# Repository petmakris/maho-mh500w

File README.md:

# Maho MH500w CNC

Documentation and notes for a Maho MH500W CNC

## Selecting Heidenhain EXE (converters for 

LS-403C has a grating period of 20μm ==> 1 μm resolution in 5 fold interpolation

# Linux CNC Installation

# Software Installation

Start of `bookworm/sid` (use xfce):

https://cdimage.debian.org/cdimage/unofficial/non-free/cd-including-firmware/

- Remove cdrom from sources: sudo nano /etc/sources.list
- `sudo apt install ethtool`

Check driver alignment:

- `lspci`
- `sudo ethtool -i enp2s0`

## Install Rods' custom kernel

6.1 exists in my NAS

- install headers
- install kernel
- `sudo apt install grub-customizer`
- `sudo apt install r8168-dkms`

# Mesa 7i97

## Network interface:

`sudo vim /etc/network/interfaces`

```
auto enp2s0
iface enp2s0 inet static
address 10.10.10.1 or 192.168.1.1
```
Restart network: `sudo systemctl restart networking`

`mesaflash --device 7i97 --addr 10.10.10.10 --readhmid`

# ??? sudo ethtool -C eth0 rx-usecs 0

# LinuxCNC

`sudo apt install linuxcnc-uspace linuxcnc-uspace-dev mesaflash`

Let it run for a while. While it is running,
in another window, check the network latency by reviewing the TMAX settings on your card

`halcmd show param hm2*tmax*`

```
Parameters:
Owner   Type  Dir         Value  Name
     7  s32   RW              0  hm2_7i97.0.read-request.tmax
     7  bit   RO          FALSE  hm2_7i97.0.read-request.tmax-increased
     7  s32   RW         704022  hm2_7i97.0.read.tmax
     7  bit   RO          FALSE  hm2_7i97.0.read.tmax-increased
     7  s32   RW          42126  hm2_7i97.0.write.tmax
     7  bit   RO          FALSE  hm2_7i97.0.write.tmax-increased
```

# Notes

[Enable outputs](https://forum.linuxcnc.org/27-driver-boards/46253-mesa-7i97-analog-out-issue#246257)

# Notes

- MAHO Original color: RAL6011

## Pull Stud

- SK40 ISO 7388 II B
  - The short pull stud for SK
  - The long for BT 

ISO Standard: https://www.iso.org/standard/68845.html

What fits to a CAT40 cone:
    Pull studs ISO 7388-3 Form UD | M16 | former norm ISO 7388 Form II B (https://bit.ly/38K9Pz4)
    Kemmler
        Order number: 404.20.16
        https://www.kemmler-shop.de/en/pull-studs/pull-studs-iso-7388/1509/pull-studs-iso-7388-3-form-ud-m16-with-drill-through-without-o-ring?c=1099

What fits to a BT40 cone:
    Longer by 3mm.
    Kemmler:
        Order number: 404.20.16.20
        https://www.kemmler-shop.de/en/pull-studs/pull-studs-iso-7388/1511/pull-studs-iso-7388-3-form-ud-m16-with-drill-through-incl.-o-ring?c=1099

# Gallery

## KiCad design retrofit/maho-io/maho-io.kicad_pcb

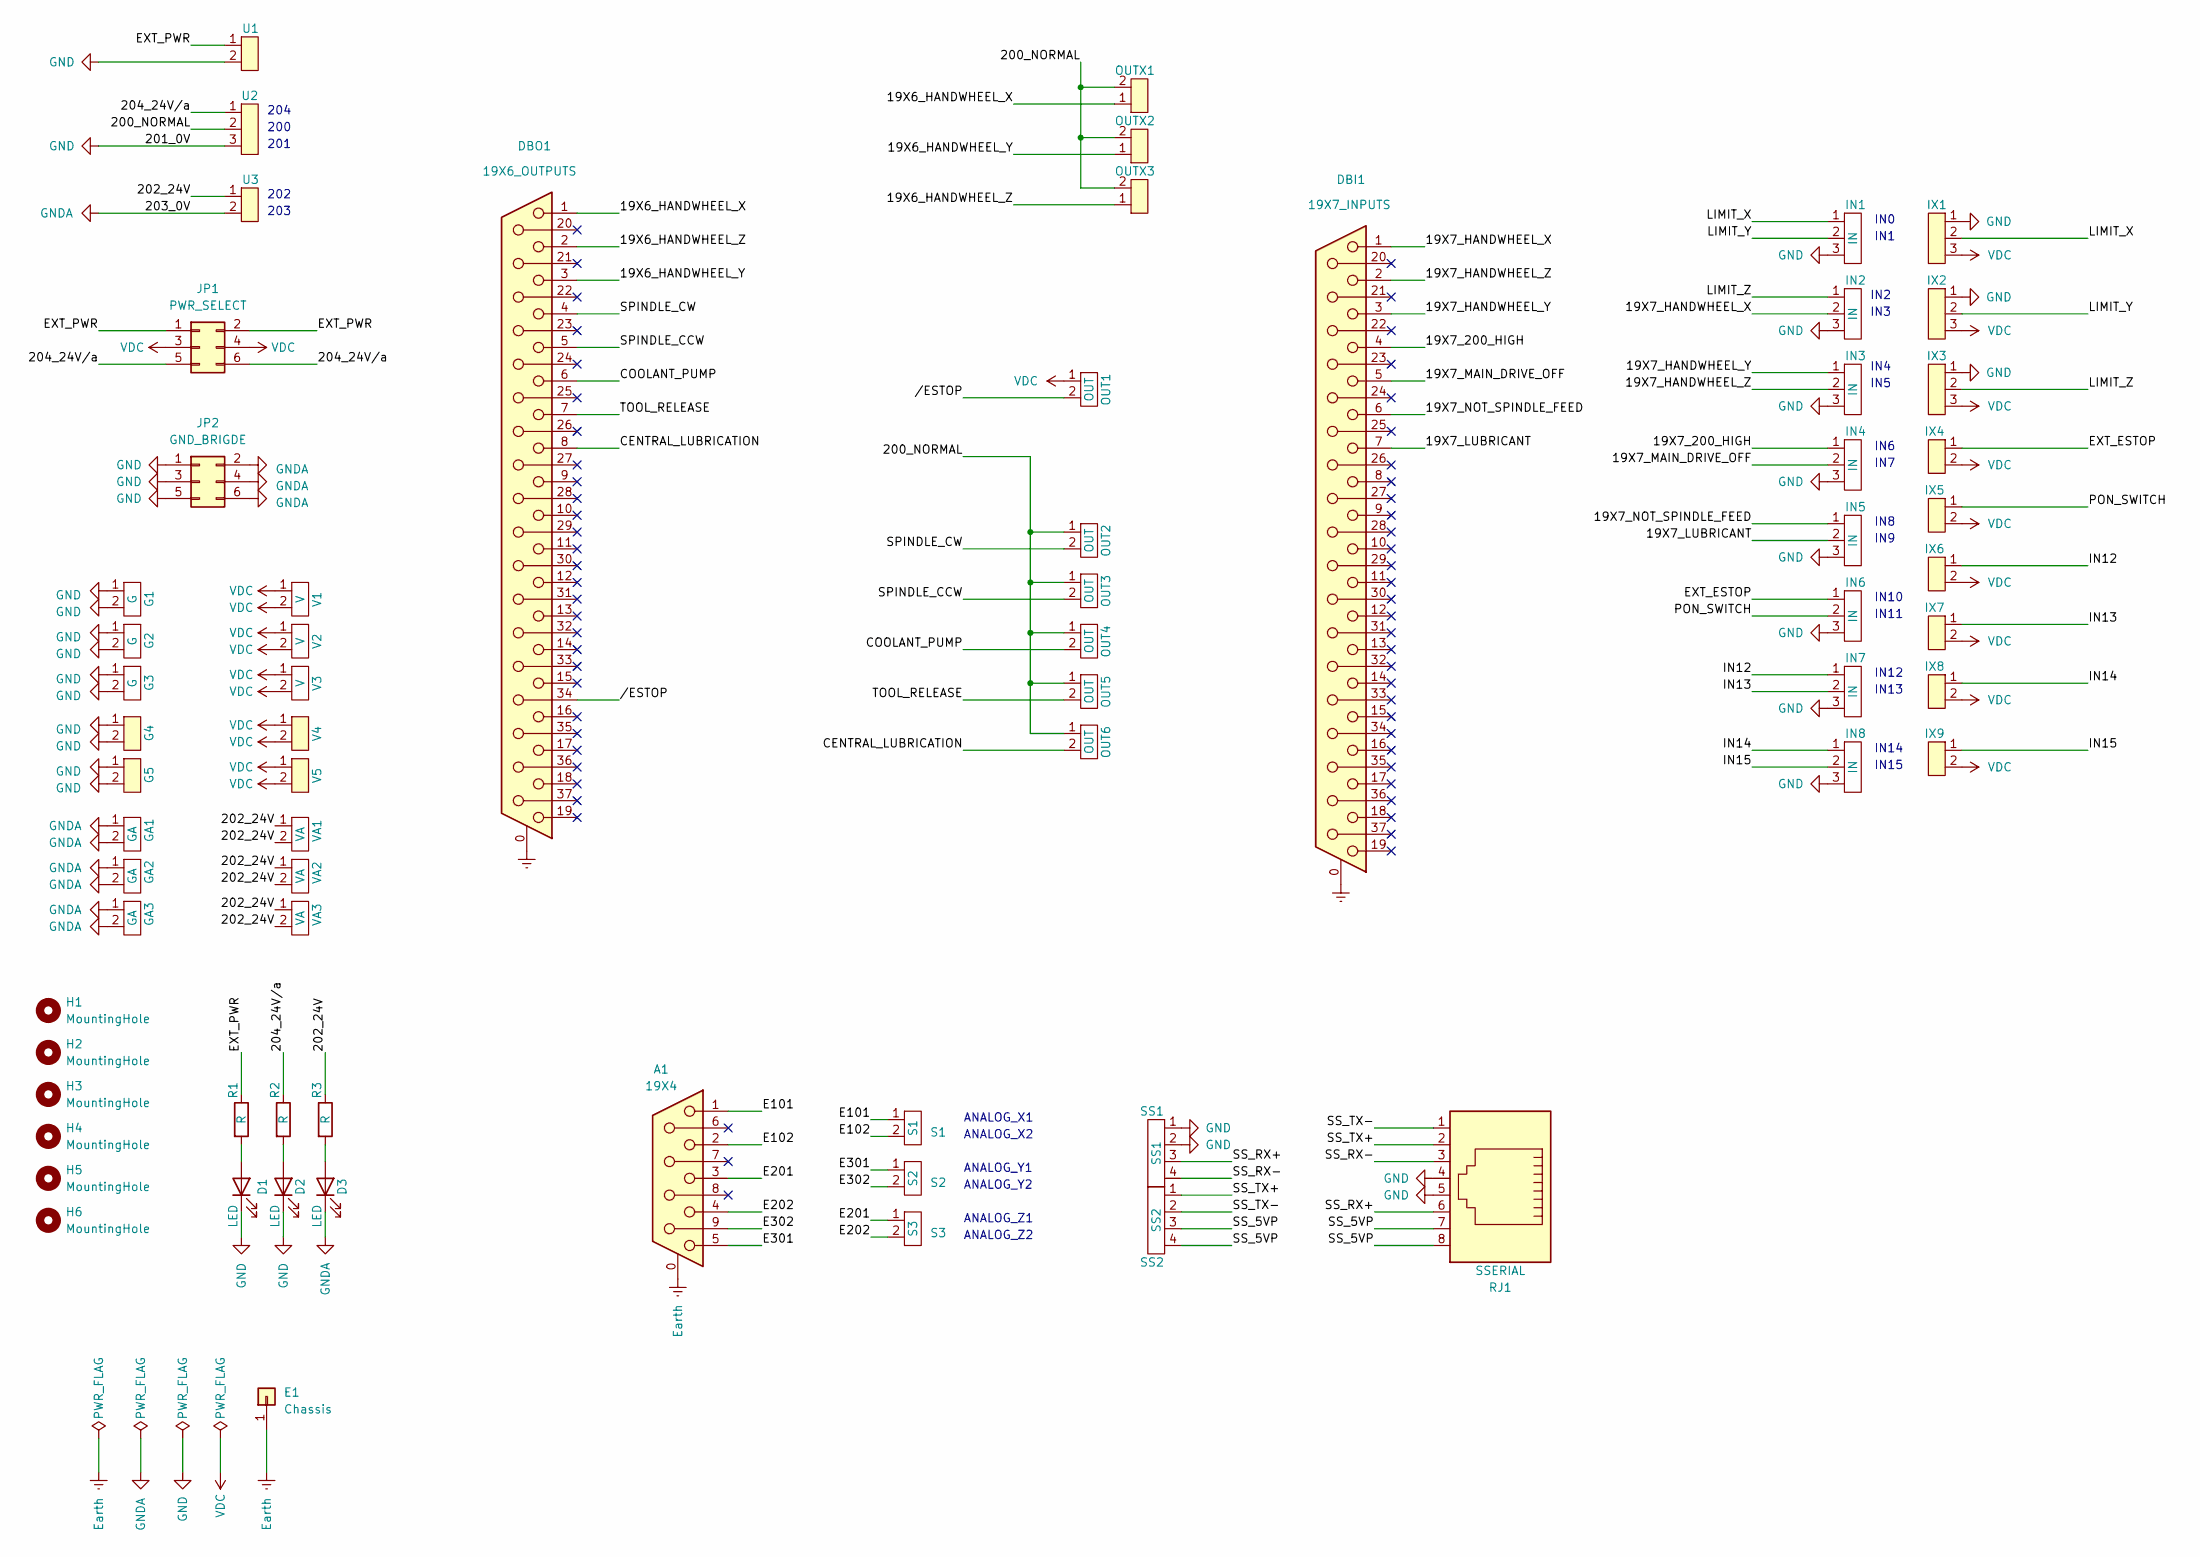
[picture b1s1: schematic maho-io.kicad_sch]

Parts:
A1: 19X4; DSUB-9_Female_Vertical_P2.77x2.84mm_MountingHoles
D1, D2, D3: LED; LED_D5.0mm
DBI1: 19X7_INPUTS; DSUB-37_Female_Vertical_P2.77x2.84mm_MountingHoles
DBO1: 19X6_OUTPUTS; DSUB-37_Female_Vertical_P2.77x2.84mm_MountingHoles
E1: Chassis; MountingHole_4.5mm_Pad
G1, G2, G3: G; XY2500V-C(5.08)-2P
G4, G5: XY2500R-C(5.08)-2P
GA1, GA2, GA3: GA; XY2500V-C(5.08)-2P
H1, H2, H3, H4, H5, H6: MountingHole; MountingHole_4.5mm
IN1, IN2, IN3, IN4, IN5, IN6, IN7, IN8: IN; XY2500V-C(5.08)-3P
IX1, IX2, IX3: XY2500R-C(5.08)-3P
IX4, IX5, IX6, IX7, IX8, IX9: XY2500R-C(5.08)-2P
JP1: PWR_SELECT; PinSocket_2x03_P2.54mm_Vertical
JP2: GND_BRIGDE; PinSocket_2x03_P2.54mm_Vertical
OUT1, OUT2, OUT3, OUT4, OUT5, OUT6: OUT; XY2500V-C(5.08)-2P
OUTX1, OUTX2, OUTX3: XY2500R-C(5.08)-2P
R1, R2, R3: R; R_0805_2012Metric
RJ1: SSERIAL; MTJ-88FX1
S1: S1; XY2500V-C(5.08)-2P
S2: S2; XY2500V-C(5.08)-2P
S3: S3; XY2500V-C(5.08)-2P
SS1: SS1; XY2500V-C(5.08)-4P
SS2: SS2; XY2500V-C(5.08)-4P
U1, U3: XY2500R-C(5.08)-2P
U2: XY2500R-C(5.08)-3P
V1, V2, V3: V; XY2500V-C(5.08)-2P
V4, V5: XY2500R-C(5.08)-2P
VA1, VA2, VA3: VA; XY2500V-C(5.08)-2P

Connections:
/19X6_HANDWHEEL_X: DBO1.1, OUTX1.1
/19X6_HANDWHEEL_Y: DBO1.3, OUTX2.1
/19X6_HANDWHEEL_Z: DBO1.2, OUTX3.1
/19X7_200_HIGH: DBI1.4, IN4.1
/19X7_HANDWHEEL_X: DBI1.1, IN2.2
/19X7_HANDWHEEL_Y: DBI1.3, IN3.1
/19X7_HANDWHEEL_Z: DBI1.2, IN3.2
/19X7_LUBRICANT: DBI1.7, IN5.2
/19X7_MAIN_DRIVE_OFF: DBI1.5, IN4.2
/19X7_NOT_SPINDLE_FEED: DBI1.6, IN5.1
/200_NORMAL: OUT2.1, OUT3.1, OUT4.1, OUT5.1, OUT6.1, OUTX1.2, OUTX2.2, OUTX3.2, U2.2
/202_24V: R3.1, U3.1, VA1.1, VA1.2, VA2.1, VA2.2, VA3.1, VA3.2
/204_24V/a: JP1.5, JP1.6, R2.1, U2.1
/CENTRAL_LUBRICATION: DBO1.8, OUT6.2
/COOLANT_PUMP: DBO1.6, OUT4.2
/E101: A1.1, S1.1
/E102: A1.2, S1.2
/E201: A1.3, S3.1
/E202: A1.4, S3.2
/E301: A1.5, S2.1
/E302: A1.9, S2.2
/EXT_ESTOP: IN6.1, IX4.1
/EXT_PWR: JP1.1, JP1.2, R1.1, U1.1
/IN12: IN7.1, IX6.1
/IN13: IN7.2, IX7.1
/IN14: IN8.1, IX8.1
/IN15: IN8.2, IX9.1
/LIMIT_X: IN1.1, IX1.2
/LIMIT_Ζ: IN2.1, IX3.2
/LIMIT_Υ: IN1.2, IX2.2
/PON_SWITCH: IN6.2, IX5.1
/SPINDLE_CCW: DBO1.5, OUT3.2
/SPINDLE_CW: DBO1.4, OUT2.2
/SS_5VP: RJ1.7, RJ1.8, SS2.3, SS2.4
/SS_RX+: RJ1.6, SS1.3
/SS_RX-: RJ1.3, SS1.4
/SS_TX+: RJ1.2, SS2.1
/SS_TX-: RJ1.1, SS2.2
/TOOL_RELEASE: DBO1.7, OUT5.2
//ESTOP: DBO1.34, OUT1.2
Earth: A1.0 (PAD), DBI1.0 (PAD), DBO1.0 (PAD), E1.1
GND: D1.1 (K), D2.1 (K), G1.1, G1.2, G2.1, G2.2, G3.1, G3.2, G4.1, G4.2, G5.1, G5.2, IN1.3, IN2.3, IN3.3, IN4.3, IN5.3, IN6.3, IN7.3, IN8.3, IX1.1, IX2.1, IX3.1, JP2.1, JP2.3, JP2.5, RJ1.4, RJ1.5, SS1.1, SS1.2, U1.2, U2.3
GNDA: D3.1 (K), GA1.1, GA1.2, GA2.1, GA2.2, GA3.1, GA3.2, JP2.2, JP2.4, JP2.6, U3.2
unnamed: D1.2 (A), R1.2
unnamed: D2.2 (A), R2.2
unnamed: D3.2 (A), R3.2
VDC: IX1.3, IX2.3, IX3.3, IX4.2, IX5.2, IX6.2, IX7.2, IX8.2, IX9.2, JP1.3, JP1.4, OUT1.1, V1.1, V1.2, V2.1, V2.2, V3.1, V3.2, V4.1, V4.2, V5.1, V5.2

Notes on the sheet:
IN12
ANALOG_Y1
ANALOG_Z1
IN7
IN4
204
IN15
IN2
201
IN13
ANALOG_Z2
ANALOG_X1
IN8
IN14
202
ANALOG_Y2
IN3
IN5
IN1
IN6
IN11
IN9
IN0
203
ANALOG_X2
IN10
200

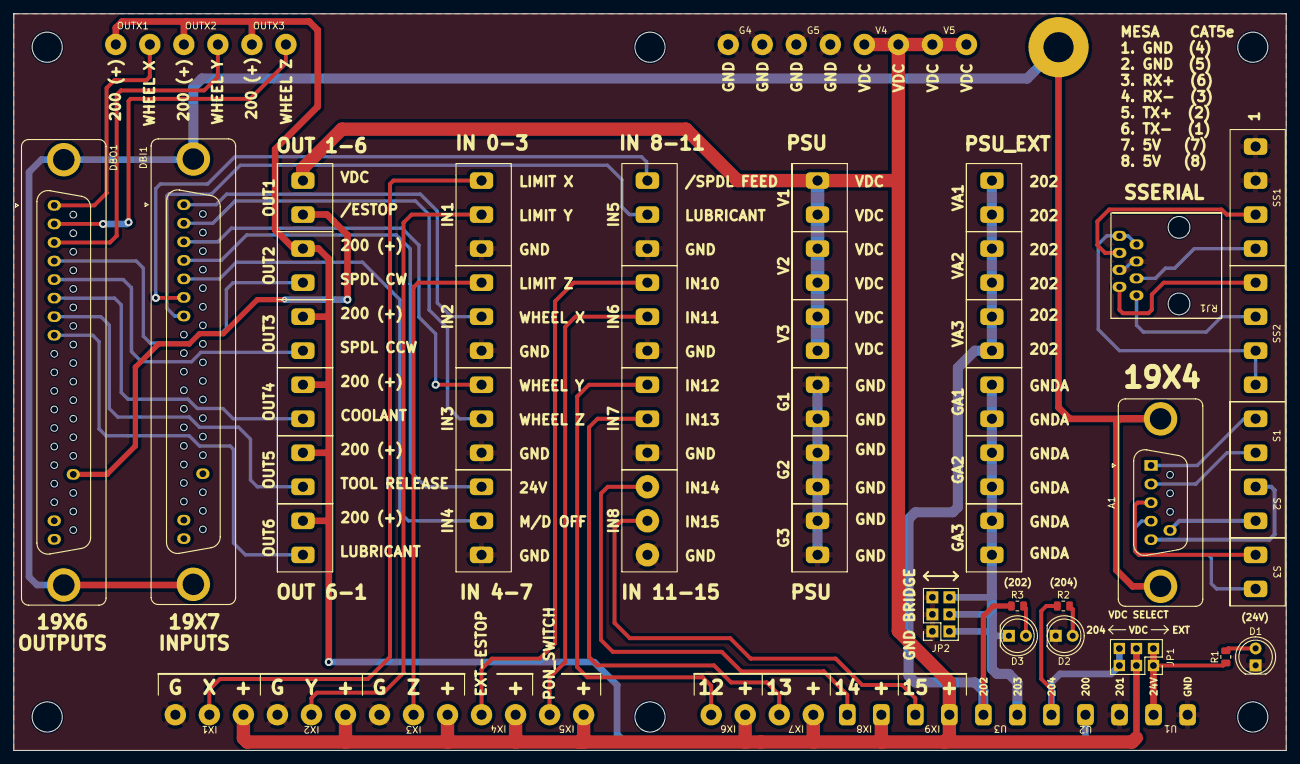
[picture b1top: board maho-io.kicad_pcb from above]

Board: 2 copper layers, 190.0 x 110.0 mm, 69 parts (0 on the bottom side), 47 nets.

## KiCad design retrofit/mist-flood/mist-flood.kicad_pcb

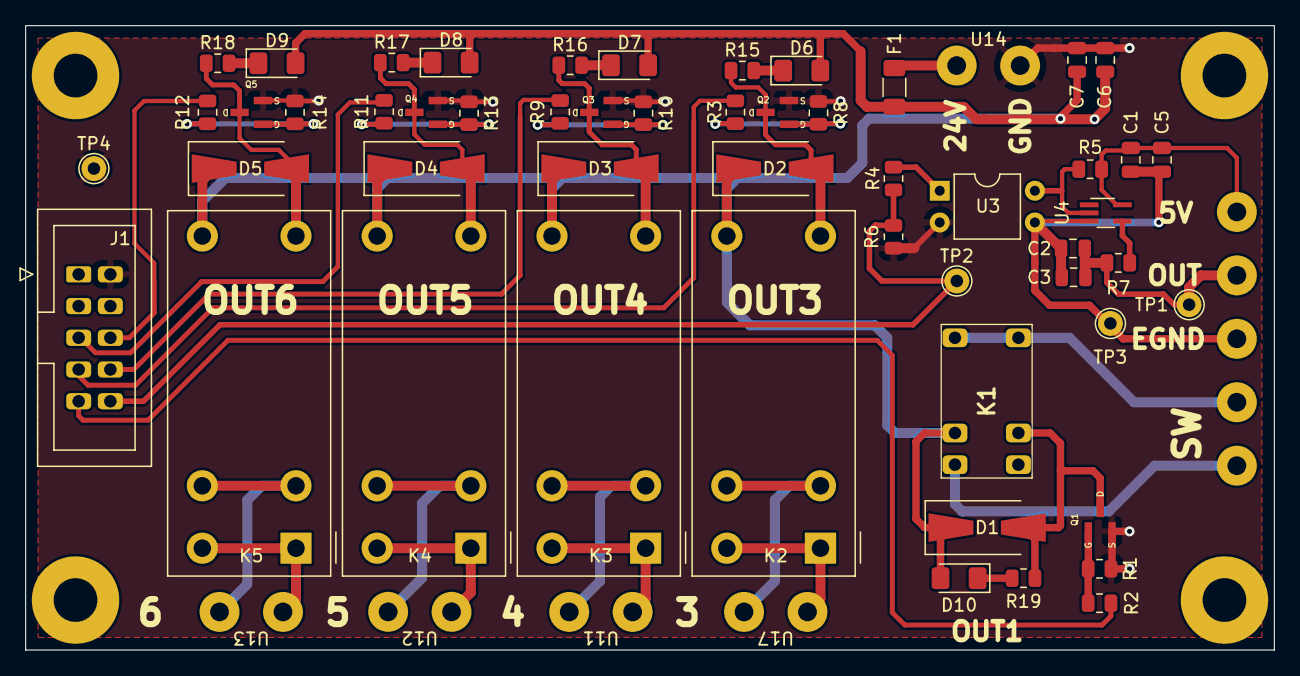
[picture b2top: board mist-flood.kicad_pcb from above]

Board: 2 copper layers, 100.0 x 50.0 mm, 64 parts (0 on the bottom side), 40 nets.

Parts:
C1, C2, C3, C5, C6, C7: 10u; C_0805_2012Metric
D1, D2, D3, D4, D5: 1N4007G-SMA; D_SMA-SMB_Universal_Handsoldering
D6, D7, D8, D9, D10: LED; LED_1206_3216Metric_Pad1.42x1.75mm_HandSolder
F1: Fuse; R_1206_3216Metric_Pad1.30x1.75mm_HandSolder
J1: Outputs; IDC-Header_2x05_P2.54mm_Vertical
J10, J11, J12, J13: Mounting Hole; MountingHole_3.5mm_Pad
K1: G5V-1-DC24
K2, K3, K4, K5: Fujitsu_FTR-F1A; Relay_DPST_Fujitsu_FTR-F1A
Q1, Q2, Q3, Q4, Q5: FDN335N; SOT-23
R1, R7, R8, R10, R13, R14: 10K; R_0805_2012Metric
R2, R3, R9, R11, R12: 47; R_0805_2012Metric
R4: 1K; R_0805_2012Metric
R5: 4K7; R_0805_2012Metric
R6: 47K; R_0805_2012Metric
R15, R16, R17, R18: 2K2; R_0805_2012Metric
R19: 680; R_0805_2012Metric
TP1: v_pwm_out; TestPoint_THTPad_D2.0mm_Drill1.0mm
TP2: V_pwm_in; TestPoint_THTPad_D2.0mm_Drill1.0mm
TP3: GNDD; TestPoint_THTPad_D2.0mm_Drill1.0mm
TP4: GND; TestPoint_THTPad_D2.0mm_Drill1.0mm
U2: XY2500R-C(5.08)-3P
U3: PC817; DIP-4_W7.62mm
U4: 74AHCT1G14SE-7; SOT-353_SC-70-5_Handsoldering
U5, U11, U12, U13, U14, U17: XY2500R-C(5.08)-2P

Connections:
+5V: C1.1, C5.1, R5.1, U2.3, U4.5
+24V: C6.2, C7.2, D1.1 (K), D2.1 (K), D3.1 (K), D4.1 (K), D5.1 (K), D6.2 (A), D7.2 (A), D8.2 (A), D9.2 (A), D10.2 (A), F1.2, K1.9, K2.5, K3.5, K4.5, K5.5
/OUT1: J1.9, R2.1
/OUT2: J1.10, R4.1, R6.1, TP2.1
/OUT3: J1.7, R3.1
/OUT4: J1.8, R9.1
/OUT5: J1.5, R11.1
/OUT6: J1.6, R12.1
/SW1C: K2.2, K2.7, U17.1
/SW1S: K2.1, K2.8, U17.2
/SW2C: K3.2, K3.7, U11.1
/SW2S: K3.1, K3.8, U11.2
/SW3C: K4.2, K4.7, U12.1
/SW3S: K4.1, K4.8, U12.2
/SW4C: K5.2, K5.7, U13.1
/SW4S: K5.1, K5.8, U13.2
/SW5C: K1.5, K1.6, U5.2
/SW5S: K1.10, U5.1
GND: C6.1, C7.1, J1.2, Q1.S, Q2.S, Q3.S, Q4.S, Q5.S, R1.2, R6.2, R8.2, R10.2, R13.2, R14.2, TP4.1, U3.2, U14.1
GNDD: C1.2, C2.2, C3.2, C5.2, TP3.1, U2.1, U3.3, U4.3
unnamed: C2.1, C3.1, R7.1, TP1.1, U2.2
unnamed: D1.2 (A), K1.2, Q1.D, R19.1
unnamed: D2.2 (A), K2.4, Q2.D, R15.1
unnamed: D3.2 (A), K3.4, Q3.D, R16.1
unnamed: D4.2 (A), K4.4, Q4.D, R17.1
unnamed: D5.2 (A), K5.4, Q5.D, R18.1
unnamed: D6.1 (K), R15.2
unnamed: D7.1 (K), R16.2
unnamed: D8.1 (K), R17.2
unnamed: D9.1 (K), R18.2
unnamed: D10.1 (K), R19.2
unnamed: F1.1, U14.2
unnamed: Q1.G, R1.1, R2.2
unnamed: Q2.G, R3.2, R8.1
unnamed: Q3.G, R9.2, R10.1
unnamed: Q4.G, R11.2, R13.1
unnamed: Q5.G, R12.2, R14.1
unnamed: R4.2, U3.1
unnamed: R5.2, U3.4, U4.2
unnamed: R7.2, U4.4

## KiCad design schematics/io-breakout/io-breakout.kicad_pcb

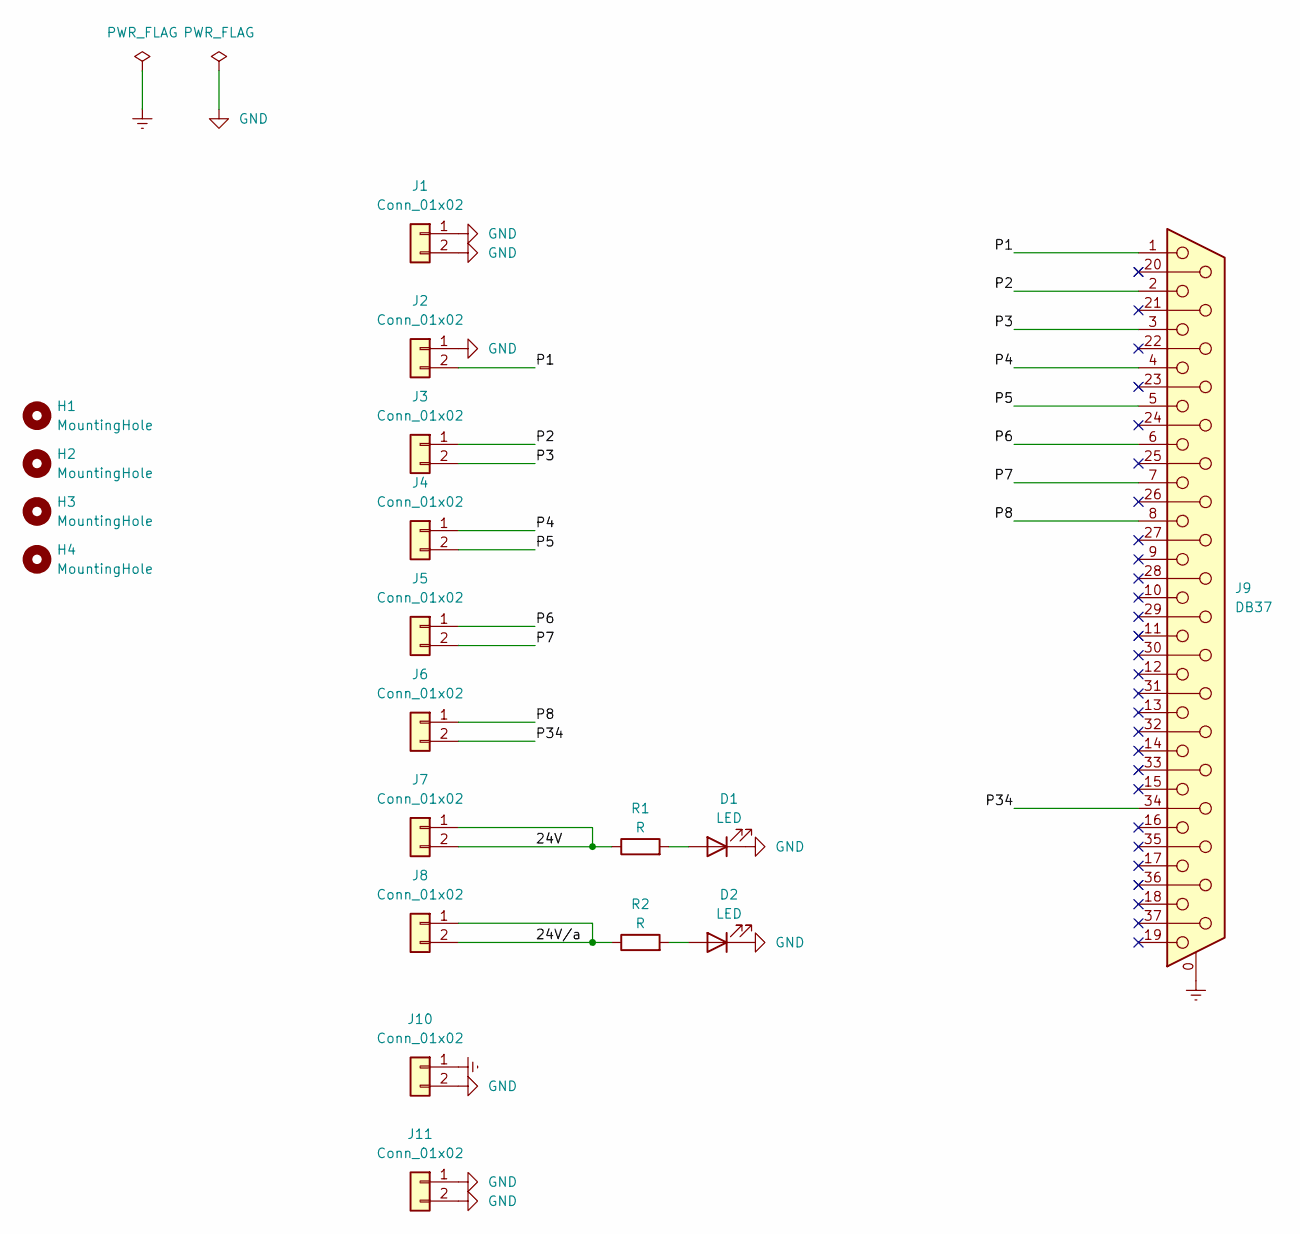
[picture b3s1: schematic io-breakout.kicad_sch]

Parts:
D1, D2: LED; LED_D5.0mm
H1, H2, H3, H4: MountingHole; MountingHole_4.5mm
J1, J2, J3, J4, J5, J6, J7, J8, J10, J11: Conn_01x02; TerminalBlock_bornier-2_P5.08mm
J9: DB37; DSUB-37_Female_Horizontal_P2.77x2.84mm_EdgePinOffset7.70mm_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
R1, R2: R; R_Axial_DIN0207_L6.3mm_D2.5mm_P10.16mm_Horizontal

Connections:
/24V: J7.1, J7.2, R1.1
/24V/a: J8.1, J8.2, R2.1
/P1: J2.2, J9.1
/P2: J3.1, J9.2
/P3: J3.2, J9.3
/P4: J4.1, J9.4
/P5: J4.2, J9.5
/P6: J5.1, J9.6
/P7: J5.2, J9.7
/P8: J6.1, J9.8
/P34: J6.2, J9.34
Earth: J9.0 (PAD), J10.1
GND: D1.1 (K), D2.1 (K), J1.1, J1.2, J2.1, J10.2, J11.1, J11.2
unnamed: D1.2 (A), R1.2
unnamed: D2.2 (A), R2.2

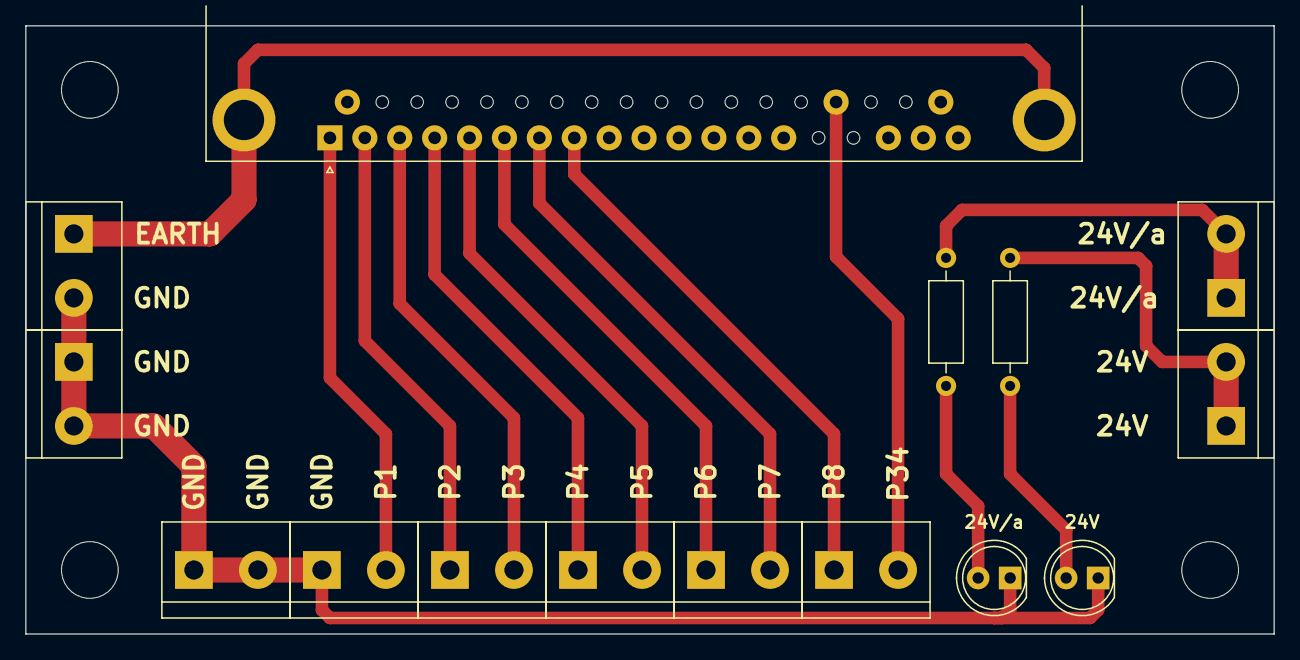
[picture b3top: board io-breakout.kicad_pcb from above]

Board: 2 copper layers, 99.1 x 48.3 mm, 19 parts (0 on the bottom side), 15 nets.

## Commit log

2023-04-10 Schematics
2023-04-11 Remove deprecated picture of estop
2023-04-13 mouse
2023-04-14 draft
2023-04-14 schematis
2023-04-15 maho-io
2023-04-15 board
2023-04-16 maho-io release for fab
2023-04-16 maho-io screenshots
2023-04-17 maho-io component and english manual
2023-04-25 updates analog
2023-05-07 updates with new board
2023-05-08 axis limits tuning
2023-05-09 test
2023-05-21 odometer
2023-06-24 udpates
2023-07-02 super upgrade
2023-07-02 adding rhino tools lib
2023-09-04 Pull Stud Information
2023-12-09 tools
2023-12-16 updates:
2024-01-14 odometer updates
2024-01-14 lubricator/odometer
2024-01-14 gitignore
2024-01-23 by the book
2024-01-25 Create LICENSE
2025-02-08 tool updates
2025-04-27 updates on tool
2025-04-30 cleanup
2025-05-01 Added nc_files
2025-10-03 chore: update on 2025-10-03 19:34:21
2025-11-26 chore: update on 2025-11-26 12:23:03
